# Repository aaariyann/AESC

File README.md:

# AESC: a regenerative, sensorless BLDC ESC

AESC is an electronic speed controller for three-phase brushless motors, built around an STM32G431. The end goal is sensorless field-oriented control with regenerative braking that pushes energy back into the battery, the same basic idea an EV traction inverter uses, just small enough to hand-solder and understand from the schematic to the last line of firmware.

It behaves like a normal RC ESC from the outside: standard 1000-2000 µs throttle input, startup beeps through the motor, throttle endpoint calibration, and an arming sequence.

## Where the project stands

| Part | Status |
|---|---|
| Hardware (schematic, 4-layer 100 x 100 mm board) | Designed |
| Firmware stage A: sensing, protection, throttle, calibration, arming, beeps | Written, builds with the feature flags off and on |
| Stage B: rotor alignment and open-loop spin | Not started |
| Stage C: sensorless FOC (observer, current loops, handover) | Not started |
| Stage D: regenerative braking with bus-voltage limiting | Not started |
| Bench results | To be added |

The motor does not spin yet. Stage A is the bring-up layer: it measures, protects and listens, and keeps every output off until it is safe to do otherwise.

## Hardware

Everything is chosen to be buyable from LCSC and solderable by hand.

| Block | Part |
|---|---|
| MCU | STM32G431CBT6 (LQFP-48, internal 16 MHz oscillator, no crystal) |
| Gate driver | DRV8300DPW (TSSOP-20, integrated bootstrap diodes, fixed 200 ns dead time) |
| Power stage | 6 x IRFR7546 (60 V, DPAK) |
| Current sensing | 10 mΩ low-side shunts, read through the G431's internal op-amps |
| 12 V rail | L78M12CDT (gate drive) |
| 3.3 V rail | AMS1117-3.3, with a ferrite bead feeding VDDA |
| Input protection | SMBJ28A TVS |
| Power connector | XT60 |

**Design target:** 4S battery, about 10 A per phase continuous. The firmware limits are set for 4S (details below). Anything higher needs the part ratings and thresholds reviewed first.

**How current is measured.** Each of the three phases has a shunt, but only phases A and B go through an op-amp (OPAMP1 on PA1, OPAMP2 on PA7). Phase C is computed from the other two. The op-amps run in PGA mode at gain 4 with a small offset network so the output rests near mid-rail and negative current can be read. That works out to roughly 23 mA per ADC count. Because the shunts are on the low side, a sample is only valid while the low-side FET is on, so the ADC is triggered at the peak of the center-aligned PWM and the duty cycle is capped at 90%.

**Pin map**

| Pin | Function |
|---|---|
| PA8, PA9, PA10 | TIM1 CH1-3, high-side inputs to the driver (INHA/B/C) |
| PB13, PB14, PB15 | TIM1 CH1N-3N, low-side inputs to the driver (INLA/B/C) |
| PA0 | Bus voltage (33 kΩ / 4.7 kΩ divider, about 26 V full scale) |
| PA1 | Phase A current (OPAMP1) |
| PA7 | Phase B current (OPAMP2) |
| PA15 | Throttle input (TIM2 CH1, PWM input mode) |
| PA11 | Status LED |
| PA13, PA14 | SWDIO, SWCLK |

## Firmware (stage A)

Built with STM32CubeIDE 1.18 and the STM32 HAL.

**Timing.** TIM1 runs center-aligned at 20 kHz with 400 ns of dead time on top of the driver's own 200 ns. The ADC conversions are triggered by TIM1 channel 4, and the ADC interrupt (20 kHz, highest priority) is where the control loop will live.

**What stage A does**

- Calibrates the current-sense offsets at startup with all outputs off, and rejects offsets that look wrong.
- Reads phase currents and bus voltage continuously.
- Latches a fault on overcurrent (instantaneous peak and a filtered continuous limit), undervoltage and overvoltage.
- Runs a 50 ms independent watchdog. Hard faults and NMI turn the outputs off, and a CPU lockup is wired to the TIM1 break input.
- Charges the bootstrap capacitors before the first run, and again after long idle periods.
- Measures the throttle pulse in hardware (period and pulse width, 1 µs resolution) and treats the signal as lost if no new pulse arrives within the timeout. A missing signal keeps the ESC disarmed. It is not treated as a fault.
- Calibrates throttle endpoints like a normal ESC and stores them in the last flash page: hold full throttle shortly after power-up, then move to minimum, then neutral.
- Arms after the throttle sits at neutral long enough.
- Plays startup, arming and calibration tones through the motor windings at low duty, and aborts immediately on overcurrent or stick movement.

**Fault codes.** When a fault latches, the status LED blinks the code, then pauses and repeats. Faults stay latched until the next power cycle.

| Blinks | Fault |
|---|---|
| 1 | Overcurrent |
| 2 | Undervoltage |
| 3 | Overvoltage |
| 4 | Throttle loss |
| 5 | Observer lost (reserved for stage C) |
| 6 | Detection or internal error |

**Feature flags.** `esc_config.h` has three switches, all defaulting to 0, so the board can be brought up in steps:

| Flag | Enables |
|---|---|
| `ESC_FEATURE_THROTTLE` | TIM2 capture, throttle reading, calibration |
| `ESC_FEATURE_BEEP` | tones through the windings |
| `ESC_FEATURE_MOTOR_STATE` | precharge, calibration entry, arming state machine |

With all three at 0 the firmware only senses and protects, and the power stage never turns on.

**Source layout**

| File | Role |
|---|---|
| `esc_config.h` | Every tunable limit and constant |
| `esc_types.h` | Fault codes, states, shared debug struct |
| `hw_pwm.c` | TIM1 setup, output enable and force-off, bootstrap precharge |
| `hw_adc.c` | Current and voltage sampling, offset calibration, protection |
| `fault.c` | Fault latching, watchdog, LED codes |
| `throttle.c` | Throttle capture, validation, calibration, flash storage |
| `beep.c` | Tone generation |
| `motor_state.c` | Arming state machine |
| `console.c` | Empty placeholder for a future UART console |

## Building and first power-up

1. Open the project in STM32CubeIDE and build the Debug configuration.
2. Flash over SWD.
3. First power-up: bench supply at 13-16 V, current limit around 0.5 A, no propeller.
4. Add `esc_debug` to Live Expressions and check:
   - `fault` stays 0
   - `adc_injection_count` climbs by about 20000 per second
   - `adc_a_offset` and `adc_b_offset` sit near 2095
   - `vbus_v` matches a multimeter
   - `ia_a` and `ib_a` read close to zero
   - `isr_cycles_max` stays well under 4000
5. Set `ESC_FEATURE_THROTTLE` to 1 and confirm `throttle_us` follows a servo tester and drops to 0 when the signal is unplugged.
6. Then enable the beep and motor-state flags.

Before any test with a real motor, remove the `__HAL_DBGMCU_FREEZE_IWDG()` line in `main.c`. It stops the watchdog at breakpoints, which is useful while debugging and wrong for anything that moves.

## Roadmap

- **Stage B:** rotor alignment and an open-loop spin-up.
- **Stage C:** sensorless FOC with Clarke and Park transforms, PI current loops, SVPWM, a back-EMF observer, and handover from open loop. Throttle above neutral commands forward torque.
- **Stage D:** regenerative braking as negative torque below neutral, scaled back as the bus approaches its limit and cut off entirely above it. Motor parameters (pole pairs, resistance, inductance) will be set in `esc_config.h`.

## Known limitations

- Overcurrent protection is software only, checked every 50 µs. There is no hardware comparator trip yet, so use a current-limited supply for early tests.
- The current trip is set at 12 A with a short debounce. That may trip during motor startup and is flagged to revisit before spinning anything.
- The throttle calibration page still needs to be reserved in the linker script. Do this before enabling the throttle feature on a firmware that has grown.
- Voltage thresholds are 12 V undervoltage, 18 V overvoltage and 17.5 V regen limit, which assume 4S. The regen limit is defined but not used yet.
- The watchdog timeout is short compared with a flash page erase, so calibration saving needs the watchdog refreshed around it (the code does this).

## Repository layout

```
hardware/   KiCad project (schematic and PCB)
firmware/   STM32CubeIDE project "AESC" (Core/Src, Core/Inc)
docs/       notes and test results
```

## Author

Built by Ariyan Siddique ([github.com/aaariyann](https://github.com/aaariyann)).

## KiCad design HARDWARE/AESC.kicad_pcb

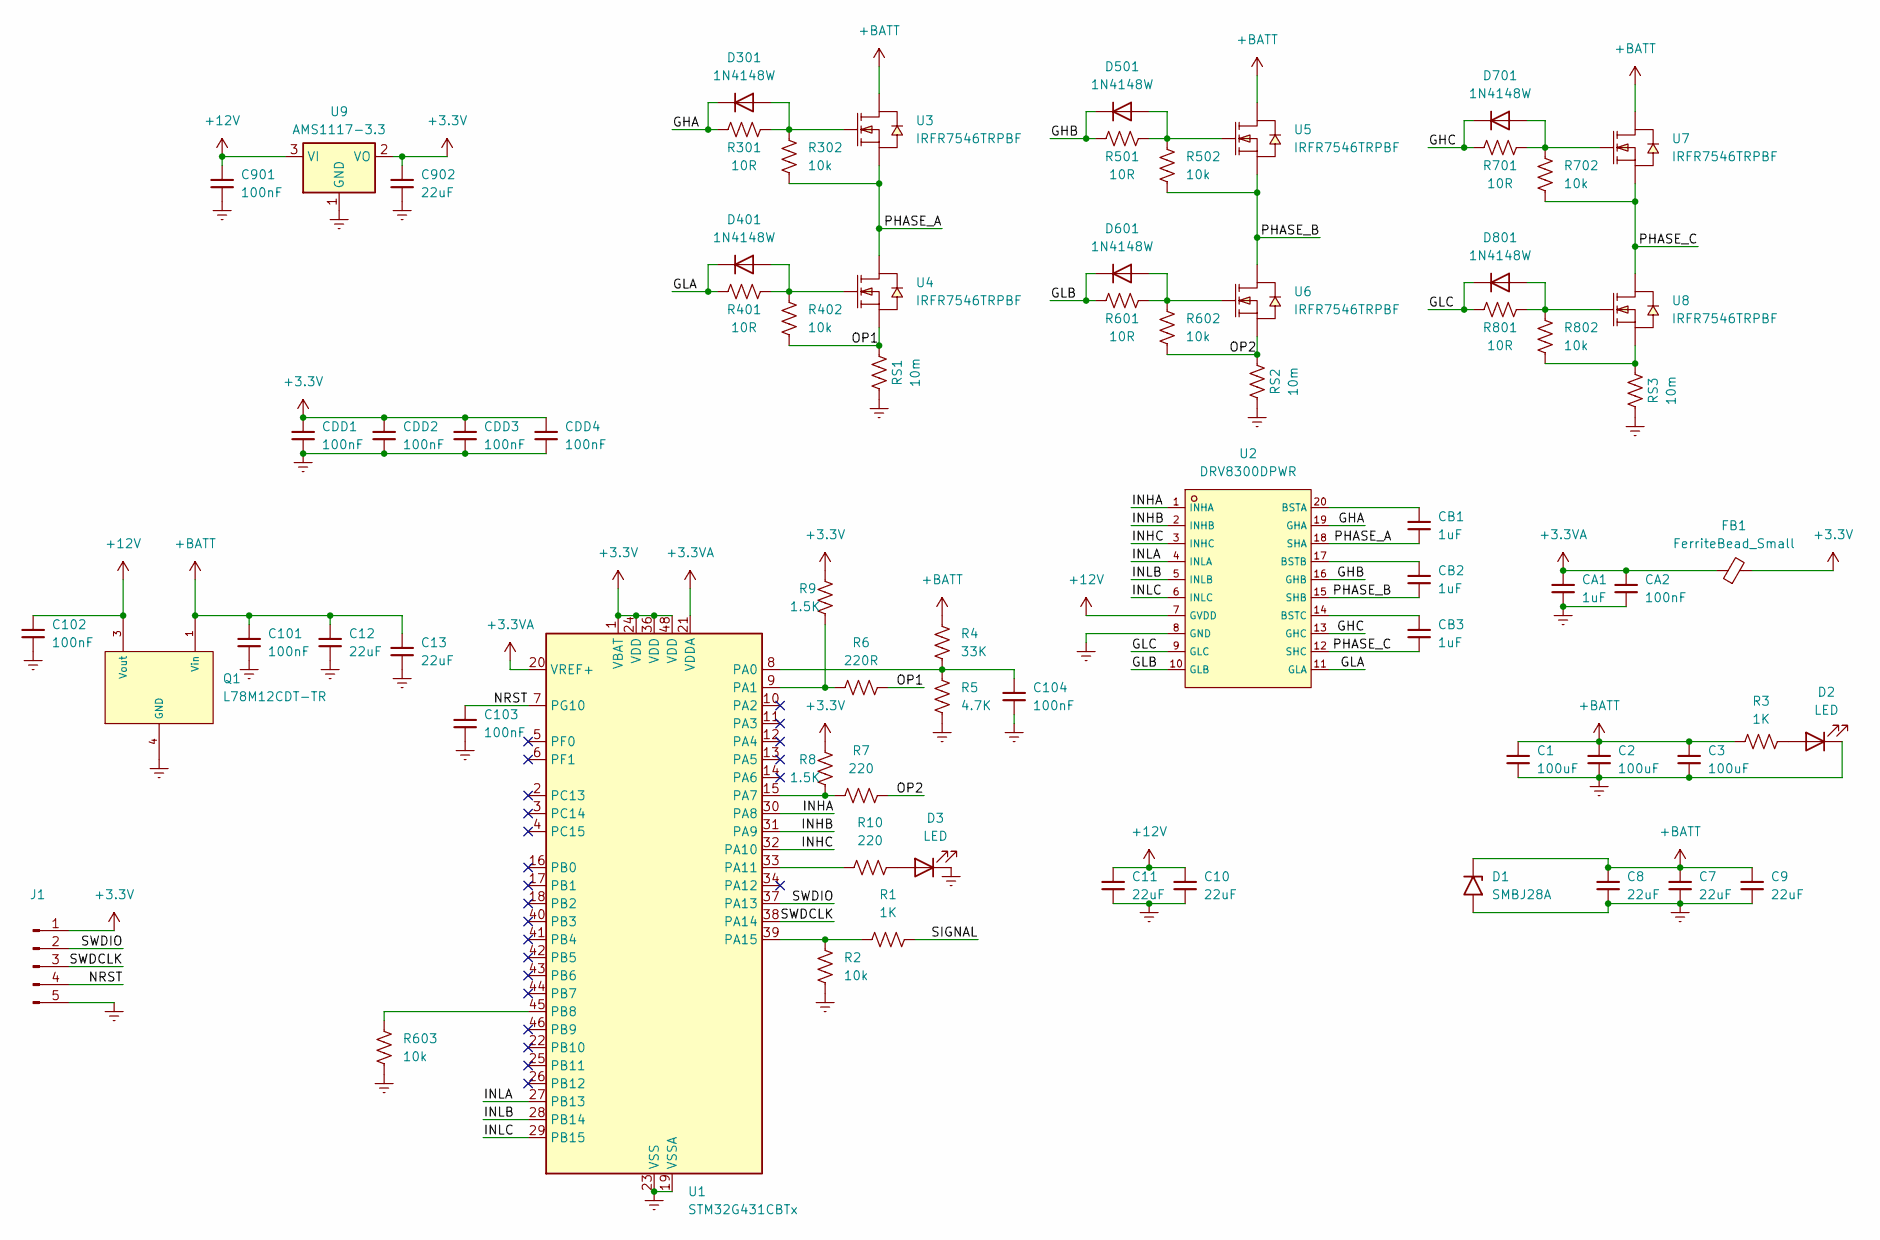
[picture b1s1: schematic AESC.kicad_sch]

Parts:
C1, C2, C3: 100uF; CP_EIA-7343-31_Kemet-D_HandSolder
C7, C8, C9, C10, C12: 22uF; C_1210_3225Metric_Pad1.33x2.70mm_HandSolder
C11, C13, C902: 22uF; CP_EIA-3528-21_Kemet-B_HandSolder
C101, C102, C103, C104, C901: 100nF; C_0805_2012Metric_Pad1.18x1.45mm_HandSolder
CA1: 1uF; C_0805_2012Metric_Pad1.18x1.45mm_HandSolder
CA2: 100nF; C_0805_2012Metric_Pad1.18x1.45mm_HandSolder
CB1, CB2, CB3: 1uF; C_0805_2012Metric_Pad1.18x1.45mm_HandSolder
CDD1, CDD2, CDD3, CDD4: 100nF; C_0805_2012Metric_Pad1.18x1.45mm_HandSolder
D1: SMBJ28A; D_SMB
D2, D3: LED; LED_1206_3216Metric_Pad1.42x1.75mm_HandSolder
D301, D401, D501, D601, D701, D801: 1N4148W; D_SOD-123
FB1: FerriteBead_Small; L_0805_2012Metric_Pad1.05x1.20mm_HandSolder
J1: Conn_01x05_Pin; PinHeader_1x05_P1.27mm_Vertical
Q1: L78M12CDT-TR; TO-252-2_L6.5-W6.1-P4.58-LS10.0-TL; LCSC C16424
R1, R3: 1K; R_0805_2012Metric_Pad1.20x1.40mm_HandSolder
R2, R302, R402, R502, R602, R603, R702, R802: 10k; R_0805_2012Metric_Pad1.20x1.40mm_HandSolder
R4: 33K; R_0805_2012Metric_Pad1.20x1.40mm_HandSolder
R5: 4.7K; R_0805_2012Metric_Pad1.20x1.40mm_HandSolder
R6: 220R; R_0805_2012Metric_Pad1.20x1.40mm_HandSolder
R7, R10: 220; R_0805_2012Metric_Pad1.20x1.40mm_HandSolder
R8, R9: 1.5K; R_0805_2012Metric_Pad1.20x1.40mm_HandSolder
R301, R401, R501, R601, R701, R801: 10R; R_0805_2012Metric_Pad1.20x1.40mm_HandSolder
RS1, RS2, RS3: 10m; R_2512_6332Metric_Pad1.40x3.35mm_HandSolder
U1: STM32G431CBTx; LQFP-48_7x7mm_P0.5mm
U2: DRV8300DPWR; TSSOP-20_L6.5-W4.4-P0.65-LS6.4-BL; LCSC C3036056
U3, U4, U5, U6, U7, U8: IRFR7546TRPBF; TO-252-3_L6.5-W5.8-P4.58-BL; LCSC C114422
U9: AMS1117-3.3; SOT-223-3_TabPin2

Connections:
+3.3V: C902.1, CDD1.1, CDD2.1, CDD3.1, CDD4.1, FB1.2, J1.1, R8.2, R9.2, U1.1 (VBAT), U1.24 (VDD), U1.36 (VDD), U1.48 (VDD), U9.2 (VO)
+3.3VA: CA1.1, CA2.1, FB1.1, U1.20 (VREF+), U1.21 (VDDA)
+12V: C10.1, C11.1, C102.1, C901.1, Q1.3 (Vout), U2.7 (GVDD), U9.3 (VI); also elsewhere on the board
+BATT: C1.1, C2.1, C3.1, C7.1, C8.1, C9.1, C12.1, C13.1, C101.1, D1.1 (A1), Q1.1 (Vin), R3.1, R4.2, U3.2 (D), U5.2 (D), U7.2 (D)
/GHA: D301.1 (K), R301.1, U2.19 (GHA)
/GHB: D501.1 (K), R501.1, U2.16 (GHB)
/GHC: D701.1 (K), R701.1, U2.13 (GHC)
/GLA: D401.1 (K), R401.1, U2.11 (GLA)
/GLB: D601.1 (K), R601.1, U2.10 (GLB)
/GLC: D801.1 (K), R801.1, U2.9 (GLC)
/INHA: U1.30 (PA8), U2.1 (INHA)
/INHB: U1.31 (PA9), U2.2 (INHB)
/INHC: U1.32 (PA10), U2.3 (INHC)
/INLA: U1.27 (PB13), U2.4 (INLA)
/INLB: U1.28 (PB14), U2.5 (INLB)
/INLC: U1.29 (PB15), U2.6 (INLC)
/NRST: C103.1, J1.4, U1.7 (PG10)
/OP1: R6.1, R402.1, RS1.2, U4.3 (S)
/OP2: R7.1, R602.1, RS2.2, U6.3 (S)
/PHASE_A: CB1.2, R302.1, U2.18 (SHA), U3.3 (S), U4.2 (D)
/PHASE_B: CB2.2, R502.1, U2.15 (SHB), U5.3 (S), U6.2 (D)
/PHASE_C: CB3.2, R702.1, U2.12 (SHC), U7.3 (S), U8.2 (D)
/SIGNAL: R1.1
/SWDCLK: J1.3, U1.38 (PA14)
/SWDIO: J1.2, U1.37 (PA13)
Earth: C1.2, C2.2, C3.2, C7.2, C8.2, C9.2, C10.2, C11.2, C12.2, C13.2, C101.2, C102.2, C103.2, C104.2, C901.2, C902.2, CA1.2, CA2.2, CDD1.2, CDD2.2, CDD3.2, CDD4.2, D1.2 (A2), D2.1 (K), D3.1 (K), J1.5, Q1.4 (GND), R2.1, R5.1, R603.1, RS1.1, RS2.1, RS3.1, U1.19 (VSSA), U1.23 (VSS), U1.35 (VSS), U1.47 (VSS), U2.8 (GND), U9.1 (GND); also elsewhere on the board
unnamed 26: D2.2 (A), R3.2; also elsewhere on the board
unnamed 27: D3.2 (A), R10.1; also elsewhere on the board
unnamed: D301.2 (A), R301.2, R302.2, U3.1 (G)
unnamed: D401.2 (A), R401.2, R402.2, U4.1 (G)
unnamed: D501.2 (A), R501.2, R502.2, U5.1 (G)
unnamed: D601.2 (A), R601.2, R602.2, U6.1 (G)
unnamed: D701.2 (A), R701.2, R702.2, U7.1 (G)
unnamed: D801.2 (A), R801.2, R802.2, U8.1 (G)
unnamed: C104.1, R4.1, R5.2, U1.8 (PA0)
unnamed: R6.2, R9.1, U1.9 (PA1)
unnamed: R7.2, R8.1, U1.15 (PA7)
unnamed: R10.2, U1.33 (PA11)
unnamed: R1.2, R2.2, U1.39 (PA15)
unnamed: R603.2, U1.45 (PB8)
unnamed: CB1.1, U2.20 (BSTA)
unnamed: CB2.1, U2.17 (BSTB)
unnamed: CB3.1, U2.14 (BSTC)
unnamed: R802.1, RS3.2, U8.3 (S)

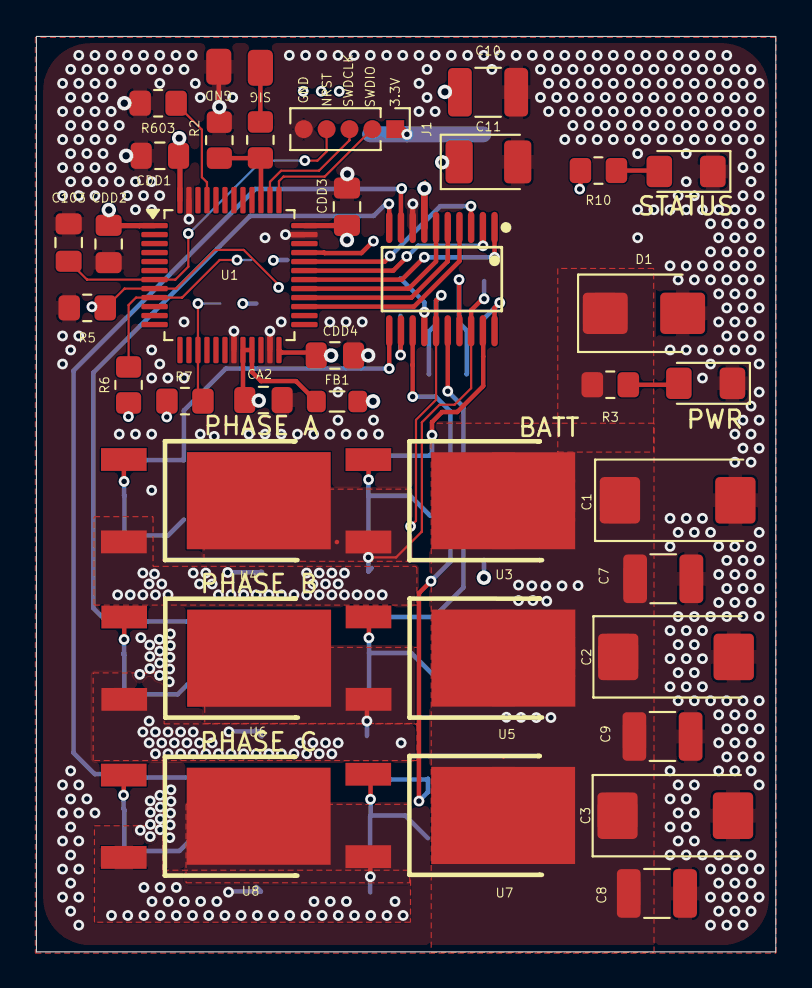
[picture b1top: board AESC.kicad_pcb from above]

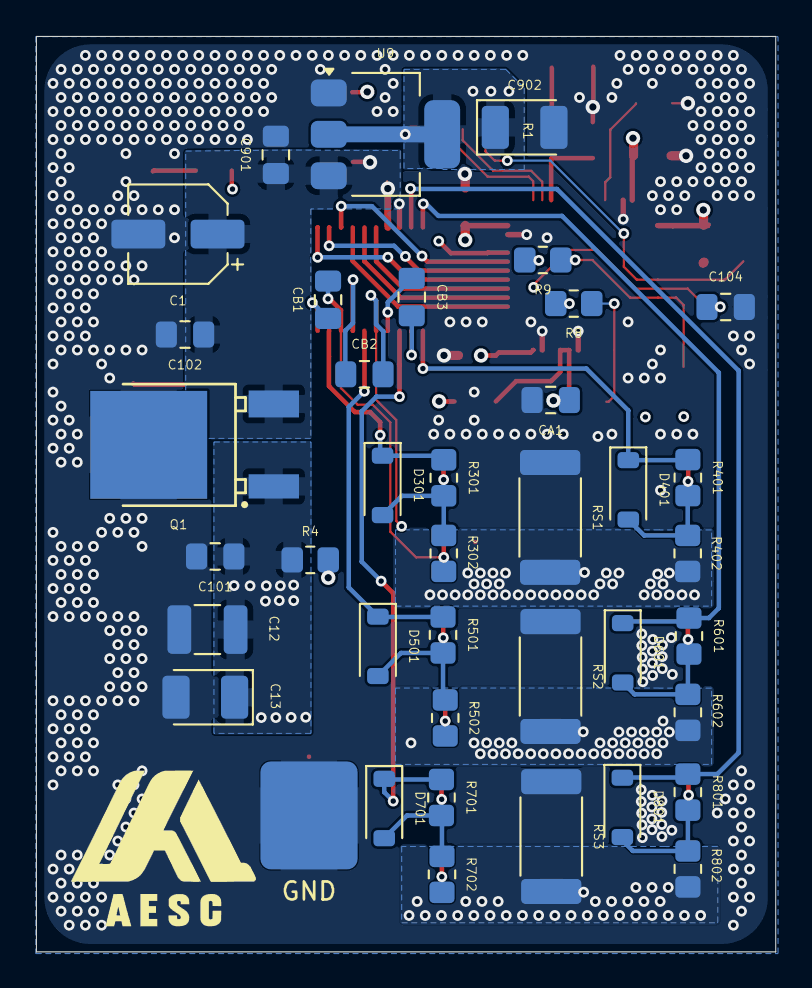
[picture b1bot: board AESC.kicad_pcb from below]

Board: 4 copper layers, 41.1 x 50.9 mm, 73 parts (38 on the bottom side), 43 nets.

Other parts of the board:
C1#2: 10uF; CP_Elec_5x5.4
PWR: LED; LED_1206_3216Metric_Pad1.42x1.75mm_HandSolder
STATUS: LED; LED_1206_3216Metric_Pad1.42x1.75mm_HandSolder

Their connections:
+12V: C1#2.1; also elsewhere on the board
Earth: C1#2.2, PWR.1 (K), STATUS.1 (K); also elsewhere on the board
unnamed 26: PWR.2 (A); also elsewhere on the board
unnamed 27: STATUS.2 (A); also elsewhere on the board

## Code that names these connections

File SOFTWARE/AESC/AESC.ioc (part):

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Mcu.Name=STM32G431C(6-8-B)Tx
Mcu.Package=LQFP48
Mcu.UserName=STM32G431CBTx
PA0.Mode=IN1-Single-Ended
PA0.Signal=ADC1_IN1
PA1.Mode=PGA_Internally_Connected
PA1.Signal=OPAMP1_VINP
PA10.GPIOParameters=GPIO_Speed
PA10.GPIO_Speed=GPIO_SPEED_FREQ_VERY_HIGH
PA10.Signal=S_TIM1_CH3
PA11.GPIOParameters=GPIO_Speed,GPIO_Label
PA11.GPIO_Label=STATUS
PA11.GPIO_Speed=GPIO_SPEED_FREQ_MEDIUM
PA11.Signal=GPIO_Output
PA13.Mode=Serial_Wire
PA13.Signal=SYS_JTMS-SWDIO
PA14.Mode=Serial_Wire
PA14.Signal=SYS_JTCK-SWCLK
PA15.GPIOParameters=GPIO_Speed
PA15.GPIO_Speed=GPIO_SPEED_FREQ_VERY_HIGH
PA15.Signal=S_TIM2_CH1
PA7.Mode=PGA_Internally_Connected
PA7.Signal=OPAMP2_VINP
PA8.GPIOParameters=GPIO_Speed
PA8.GPIO_Speed=GPIO_SPEED_FREQ_VERY_HIGH
PA8.Signal=S_TIM1_CH1
PA9.GPIOParameters=GPIO_Speed
PA9.GPIO_Speed=GPIO_SPEED_FREQ_VERY_HIGH
PA9.Signal=S_TIM1_CH2
PB13.GPIOParameters=GPIO_Speed
PB13.GPIO_Speed=GPIO_SPEED_FREQ_VERY_HIGH
PB13.Mode=PWM Generation1 CH1 CH1N
PB13.Signal=TIM1_CH1N
PB14.GPIOParameters=GPIO_Speed
PB14.GPIO_Speed=GPIO_SPEED_FREQ_VERY_HIGH
PB14.Mode=PWM Generation2 CH2 CH2N
PB14.Signal=TIM1_CH2N
PB15.GPIOParameters=GPIO_Speed
PB15.GPIO_Speed=GPIO_SPEED_FREQ_VERY_HIGH
PB15.Mode=PWM Generation3 CH3 CH3N
PB15.Signal=TIM1_CH3N
RCC.HSE_VALUE=8000000
RCC.SYSCLKFreq_VALUE=170000000
RCC.SYSCLKSource=RCC_SYSCLKSOURCE_PLLCLK
board=custom
